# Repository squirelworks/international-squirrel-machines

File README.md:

# International Squirrel Machines (ISM)

Pure Squirrel-OS/2 Warp-style hardware development.

**International Squirrel Machines** is the hardware companion line to Squirrel-OS/2. All devices are designed and developed independently (contemporary sources studied only as reference). Designs live here as KiCad projects and parametric 3D-printable shells.

## Device Line

| Device | Status | Directory |
|--------|--------|-----------|
| Keyboard | Scaffolded | `keyboard/` |
| Mouse | Planned | `mouse/` |
| Monitor | Planned | `monitor/` |
| Computer Case | Planned | `case/` |
| Motherboard | Planned | `motherboard/` |
| CPU | Planned | `cpu/` |
| Memory (RAM modules) | Scaffolded | `memory/` |
| Graphics Card | Planned | `graphics-card/` |
| Typewriter | Planned | `typewriter/` |
| Printer | Planned | `printer/` |
| Plotter | Planned | `plotter/` |
| Camera | Planned | `camera/` |
| Trackball | Planned | `trackball/` |
| Sound Card | Planned | `sound-card/` |
| Network Card | Planned | `network-card/` |
| Terminal | Planned | `terminal/` |
| Macro Pad | Planned | `macro-pad/` |
| Drawing Pads (range) | Scaffolded | `drawing-pads/` |
| Fighter Jet | Design program | `fighter-jet/` |

## Repository Layout

```
international-squirrel-machines/
├── README.md
├── docs/
│   ├── roadmap.md
│   ├── design-principles.md
│   ├── branding.md
│   └── devices/
├── common/
│   ├── footprints/
│   ├── libraries/
│   └── branding/
├── keyboard/
│   ├── README.md
│   ├── kicad/
│   └── shell/
├── fighter-jet/
│   ├── README.md
│   ├── kicad/
│   └── shell/
└── [device]/
```

## Getting Started

1. Clone this repository.
2. Open device directories for KiCad projects or OpenSCAD shells.
3. See `docs/roadmap.md` for the current development sequence.
4. Issues track every device scaffold and implementation milestone.

## Philosophy

- Pure Squirrel-OS/2 development.
- When in doubt, scaffold.
- If scaffolded, implement.
- If implemented, polish.
- If polished, inquire for the next release.

Part of the Squirrelworks family alongside [squirrelbios](https://github.com/squirelworks/squirrelbios).

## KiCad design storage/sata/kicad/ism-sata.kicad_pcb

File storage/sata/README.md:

# ISM SATA

SATA carrier for commodity drives. Original International Squirrel Machines design.

Generate: `python3 scripts/build_sata.py` — **ERC 0 / DRC 0**.

## Layout

| Block | Notes |
|-------|--------|
| Host | USB-C (`J1`) bring-up |
| MCU | RP2040 module (`U1`) — DET / ACT |
| SATA | `ISM_SATA7` (`J2`) — GNDs wired; A/B pairs stubbed |
| Power | `J3` 1×4 drive +5V/GND (+12V external) |
| Shell | Carrier + lid |

## Fab ordering

1. `python3 scripts/build_sata.py`
2. Upload `storage/sata/fab/ism-sata-gerbers.zip`
3. SMT: CPL + `BOM.csv`
4. `cd storage/sata/shell && ./export.sh`

### Off-board BOM

- Commodity 2.5"/3.5" SATA drive
- M2 screws (4×)
- Optional external +12V for 3.5" spindles

## Flash

```bash
cd storage/sata/firmware
mkdir -p build && cd build && cmake .. && make -j
# copy ism_sata.uf2 to RPI-RP2
```

VID/PID **0x1209 / 0x001E**.

## Steve interface

See `interfaces/sata.yaml`.

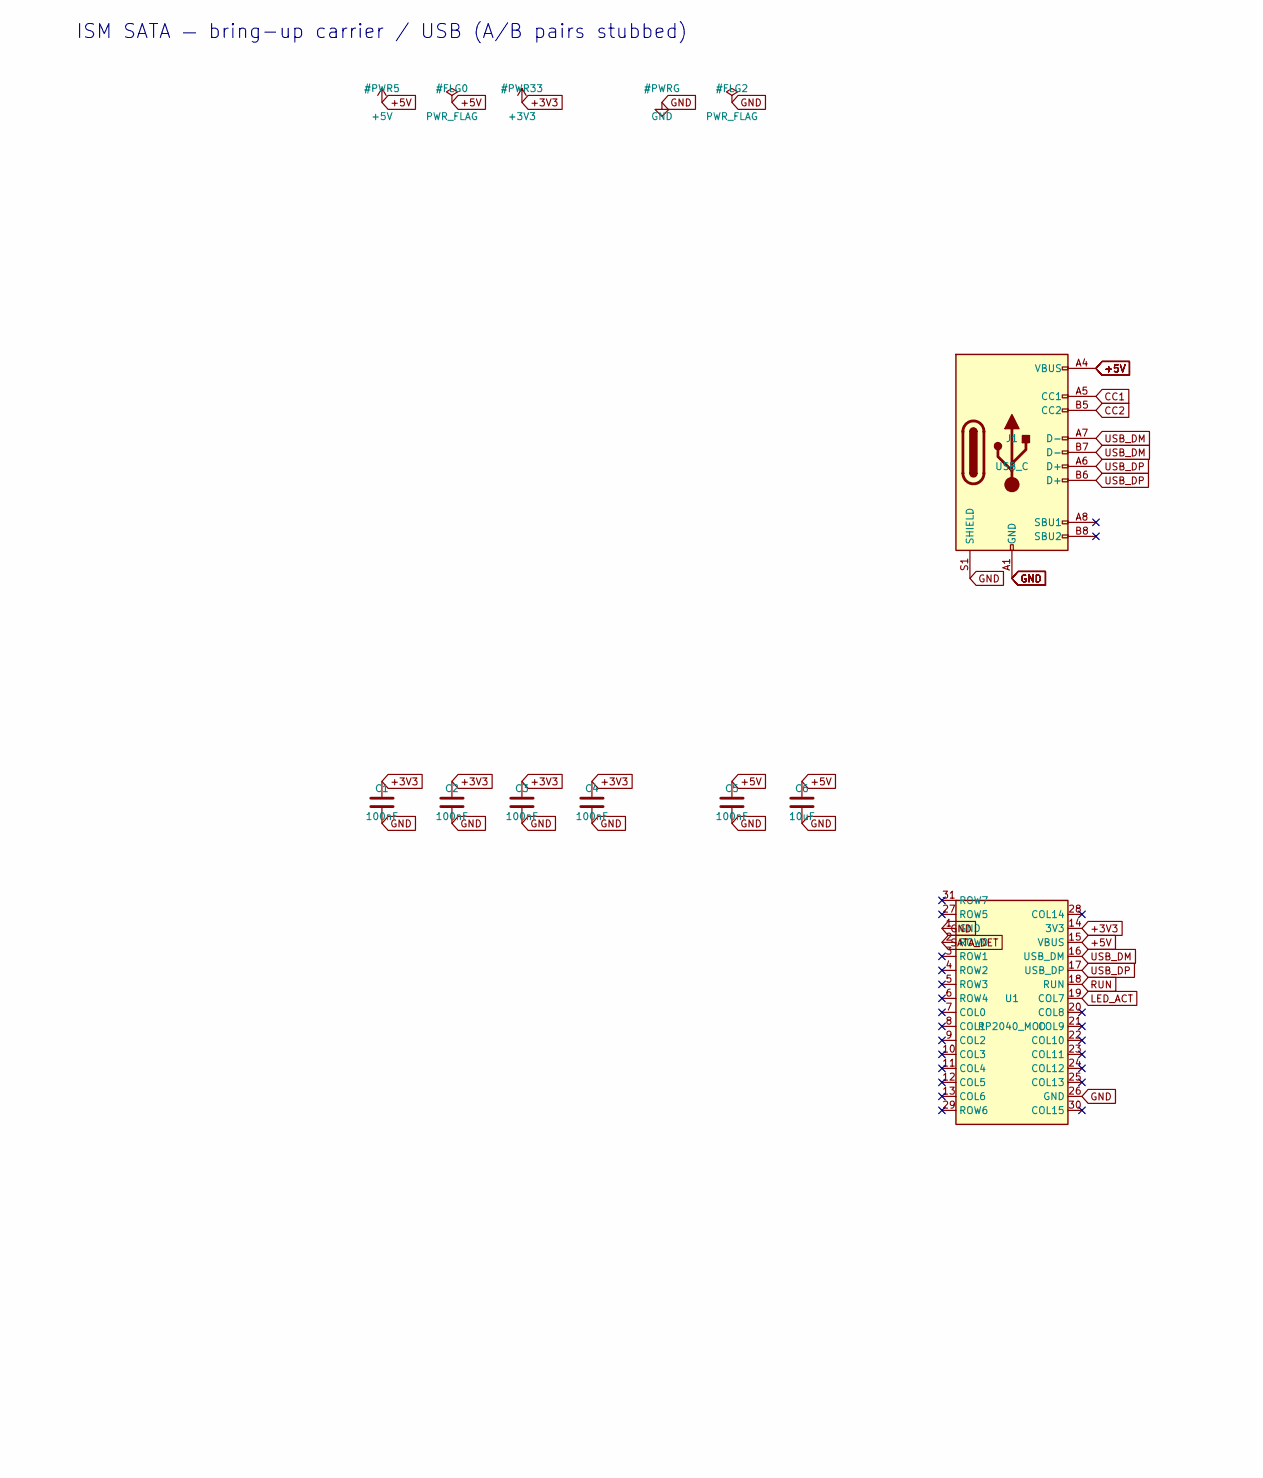
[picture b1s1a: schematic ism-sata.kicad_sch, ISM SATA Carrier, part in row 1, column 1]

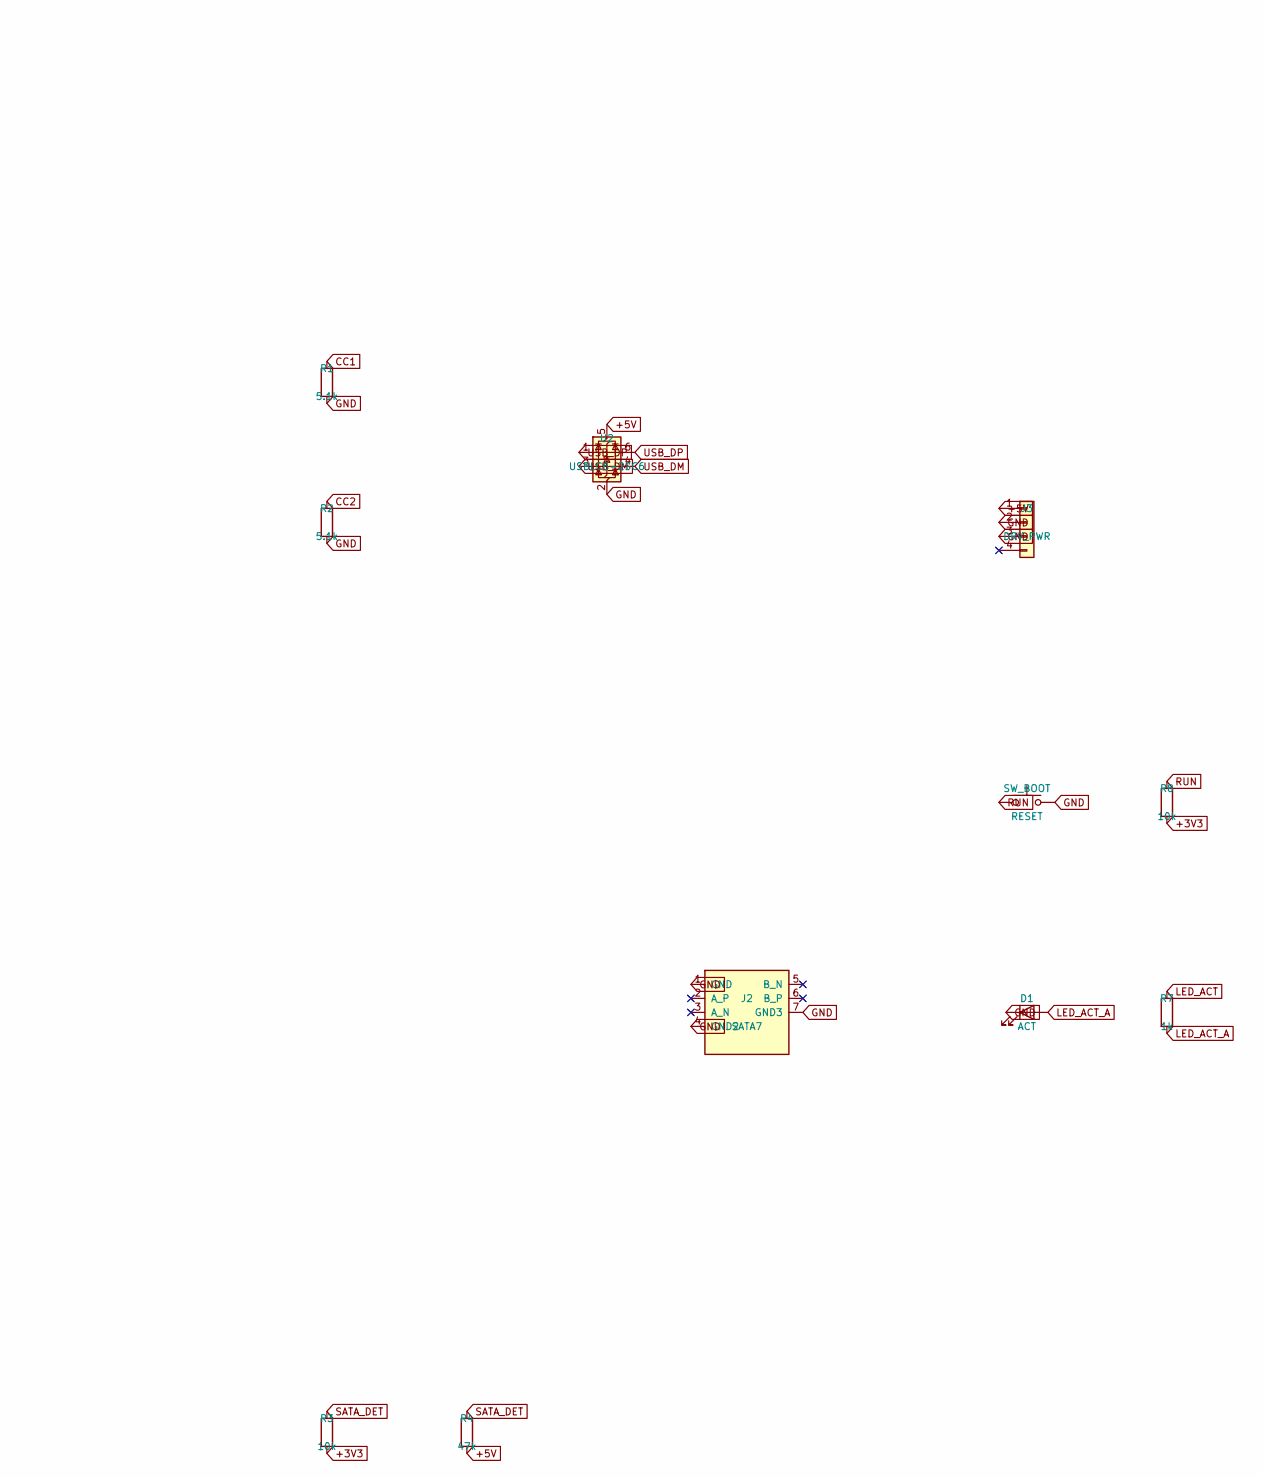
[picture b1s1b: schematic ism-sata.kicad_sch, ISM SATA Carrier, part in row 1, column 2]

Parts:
C1, C2, C3, C4, C5: 100nF; C_0603_1608Metric; LCSC C14663
C6: 10uF; C_0805_2012Metric; LCSC C15850
D1: ACT; LED_0603_1608Metric; LCSC C2286
J1: USB_C; USB_C_Receptacle_GCT_USB4105-xx-A_16P_TopMnt_Horizontal; LCSC C165948
J2: SATA7; ISM_SATA7; MPN ISM-SATA7
J3: DRV_PWR; PinHeader_1x04_P2.54mm_Vertical
R1, R2: 5.1k; R_0603_1608Metric; LCSC C23244
R3, R8: 10k; R_0603_1608Metric; LCSC C25804
R4: 47k; R_0603_1608Metric; LCSC C25803
R7: 1k; R_0603_1608Metric; LCSC C21190
SW_BOOT: RESET; SW_SPST_PTS645; LCSC C318884
U1: RP2040_MOD; ISM_RP2040_Module; MPN ISM-RP2040-MOD
U2: USBLC6-2SC6; SOT-666; LCSC C7519

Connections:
+3V3: C1.1, C2.1, C3.1, C4.1, R3.2, R8.2, U1.14 (3V3)
+5V: C5.1, C6.1, J1.A4 (VBUS), J1.A9 (VBUS), J1.B4 (VBUS), J1.B9 (VBUS), J3.1, R4.2, U1.15 (VBUS), U2.5 (VBUS)
CC1: J1.A5 (CC1), R1.1
CC2: J1.B5 (CC2), R2.1
GND: C1.2, C2.2, C3.2, C4.2, C5.2, C6.2, D1.1 (K), J1.A1 (GND), J1.A12 (GND), J1.B1 (GND), J1.B12 (GND), J1.S1 (SHIELD), J2.1 (GND), J2.4 (GND2), J2.7 (GND3), J3.2, J3.3, R1.2, R2.2, SW_BOOT.2, U1.1 (GND), U1.26 (GND), U2.2 (GND)
LED_ACT: R7.1, U1.19 (COL7)
LED_ACT_A: D1.2 (A), R7.2
RUN: R8.1, SW_BOOT.1, U1.18 (RUN)
SATA_DET: R3.1, R4.1, U1.2 (ROW0)
USB_DM: J1.A7 (D-), J1.B7 (D-), U1.16 (USB_DM), U2.3 (I/O2), U2.4 (I/O2)
USB_DP: J1.A6 (D+), J1.B6 (D+), U1.17 (USB_DP), U2.1 (I/O1), U2.6 (I/O1)

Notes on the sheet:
ISM SATA — bring-up carrier / USB (A/B pairs stubbed)

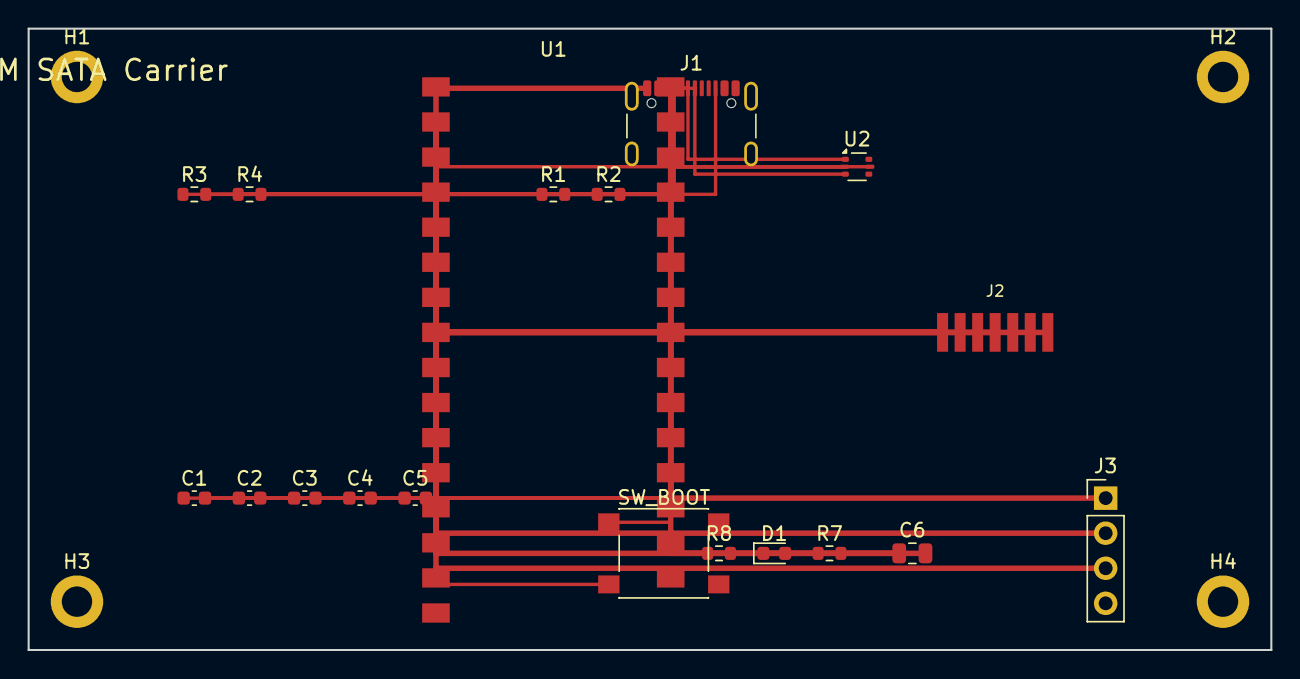
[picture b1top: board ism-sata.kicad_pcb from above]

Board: 4 copper layers, 90.0 x 45.0 mm, 23 parts (0 on the bottom side), 11 nets.

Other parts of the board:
H1, H2, H3, H4: M2; MountingHole_2.2mm_M2_DIN965_Pad

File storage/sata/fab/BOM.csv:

Designator,Value,Footprint,Quantity,Manufacturer,MPN,LCSC,Notes
U1,RP2040_MOD,ISM_RP2040_Module,1,ISM,ISM-RP2040-MOD,,No LCSC — activity / DET controller
U2,USBLC6-2SC6,SOT-666,1,ST,USBLC6-2SC6,C7519,ESD
J1,USB4105,GCT USB-C 16P,1,GCT,USB4105-GF-A,C165948,
J2,ISM_SATA7,ISM_SATA7,1,ISM,ISM-SATA7,,No LCSC — simplified SATA data; fab as custom or substitute SATA receptacle
J3,1x04,PinHeader_1x04,1,,,,Drive +5V/GND (+12V external)
"R1,R2",5.1k,0603,2,,5.1k,C23244,CC
"R3,R8",10k,0603,2,,10k,C25804,
R4,47k,0603,1,,47k,C25803,DET from +5V
R7,1k,0603,1,,1k,C21190,
C1-C5,100nF,0603,5,,100nF,C14663,
C6,10uF,0805,1,,10uF,C15850,
D1,LED,0603,1,,LED,C2286,
SW_BOOT,PTS645,PTS645,1,,PTS645,C318884,
H1-H4,M2,MountingHole,4,,,,No LCSC — mechanical NPTH

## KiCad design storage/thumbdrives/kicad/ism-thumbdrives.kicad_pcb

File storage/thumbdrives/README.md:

# ISM Thumb Drives

USB-MSC stick board wrapping commodity SPI NOR flash. Original International Squirrel Machines design.

Generate: `python3 scripts/build_thumbdrives.py` — **ERC 0 / DRC 0**.

## Layout

| Block | Notes |
|-------|--------|
| Host | USB-C (`J1`) bring-up |
| MCU | RP2040 module (`U1`) — SPI master / MSC controller |
| Media | Winbond **W25Q32JVSS** SOIC-8 (`U3`, LCSC **C82307**) |
| Shell | Stick body + end cap |

## Fab ordering

1. `python3 scripts/build_thumbdrives.py`
2. Upload `storage/thumbdrives/fab/ism-thumbdrives-gerbers.zip`
3. SMT: CPL + `BOM.csv`
4. `cd storage/thumbdrives/shell && ./export.sh`

### Off-board BOM

- M2 screws (4×)

## Flash

```bash
cd storage/thumbdrives/firmware
mkdir -p build && cd build && cmake .. && make -j
# copy ism_thumbdrives.uf2 to RPI-RP2
```

VID/PID **0x1209 / 0x001A**.

## Steve interface

See `interfaces/thumbdrives.yaml`. Activity LED heartbeat until MSC lands.

## Related

- [#53](https://github.com/squirelworks/international-squirrel-machines/issues/53) · umbrella [#49](https://github.com/squirelworks/international-squirrel-machines/issues/49)
- Follow-ups: [#225](https://github.com/squirelworks/international-squirrel-machines/issues/225)

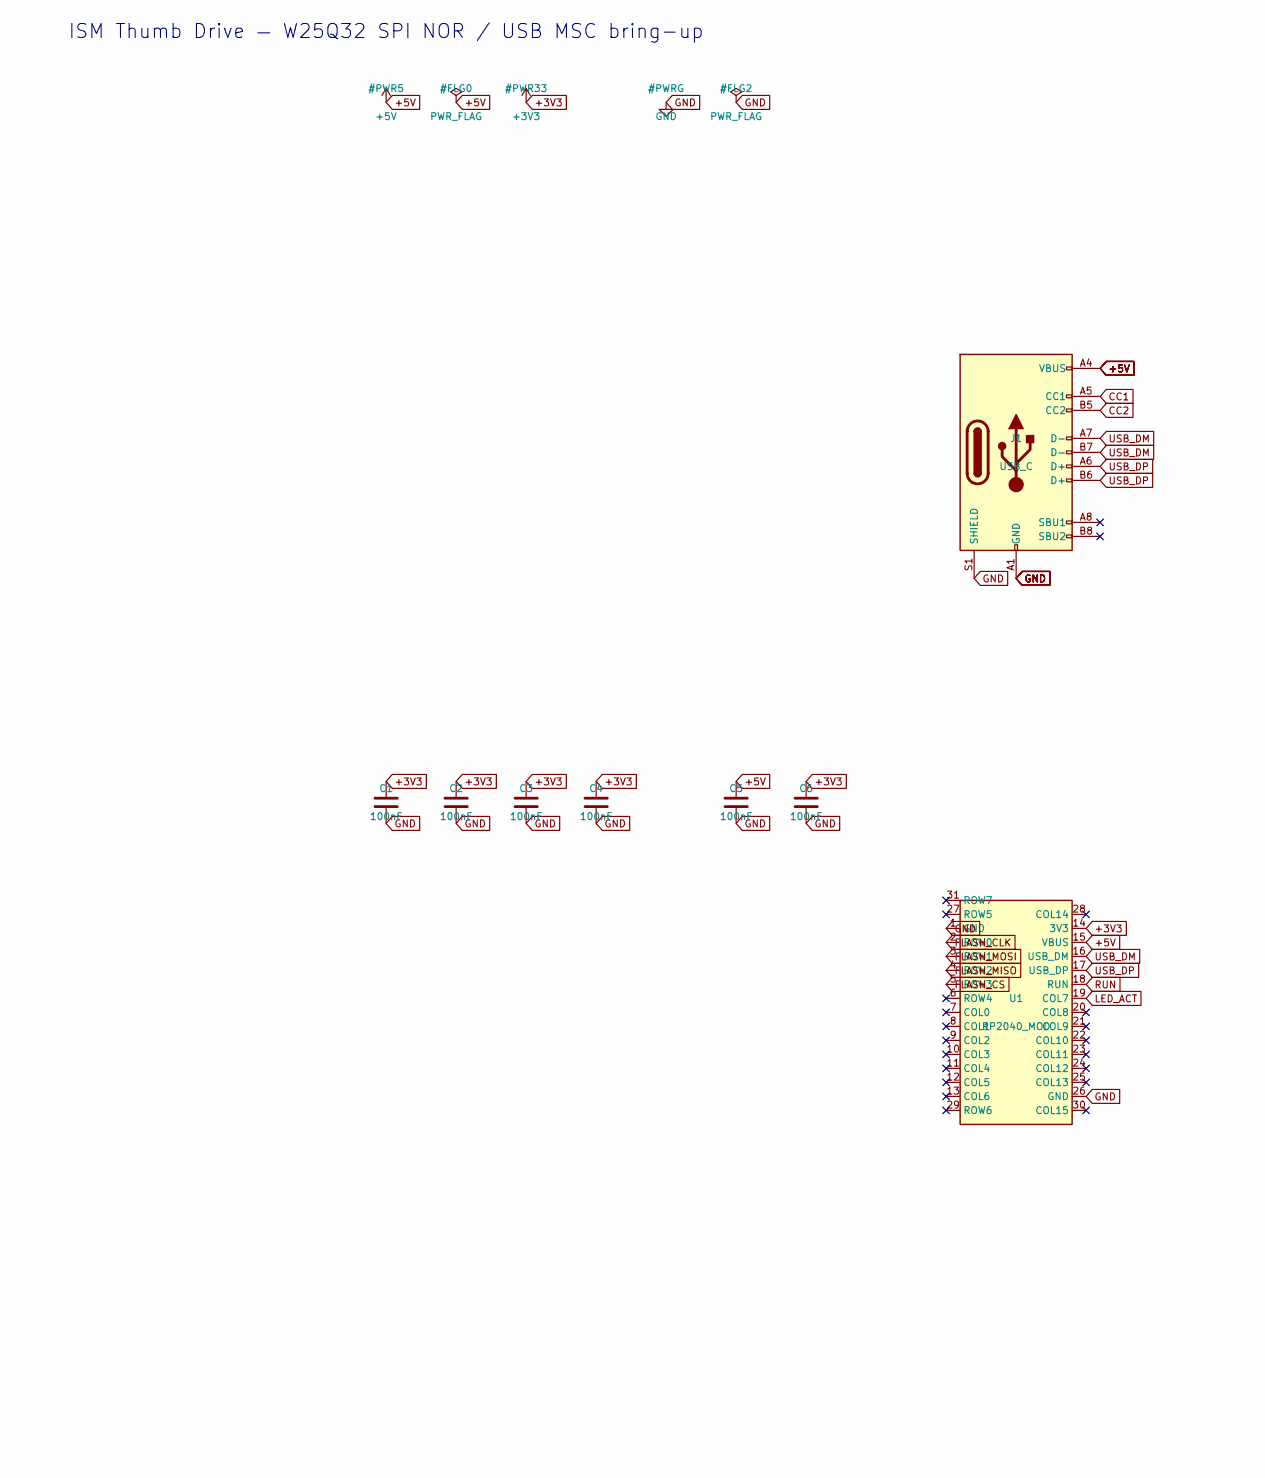
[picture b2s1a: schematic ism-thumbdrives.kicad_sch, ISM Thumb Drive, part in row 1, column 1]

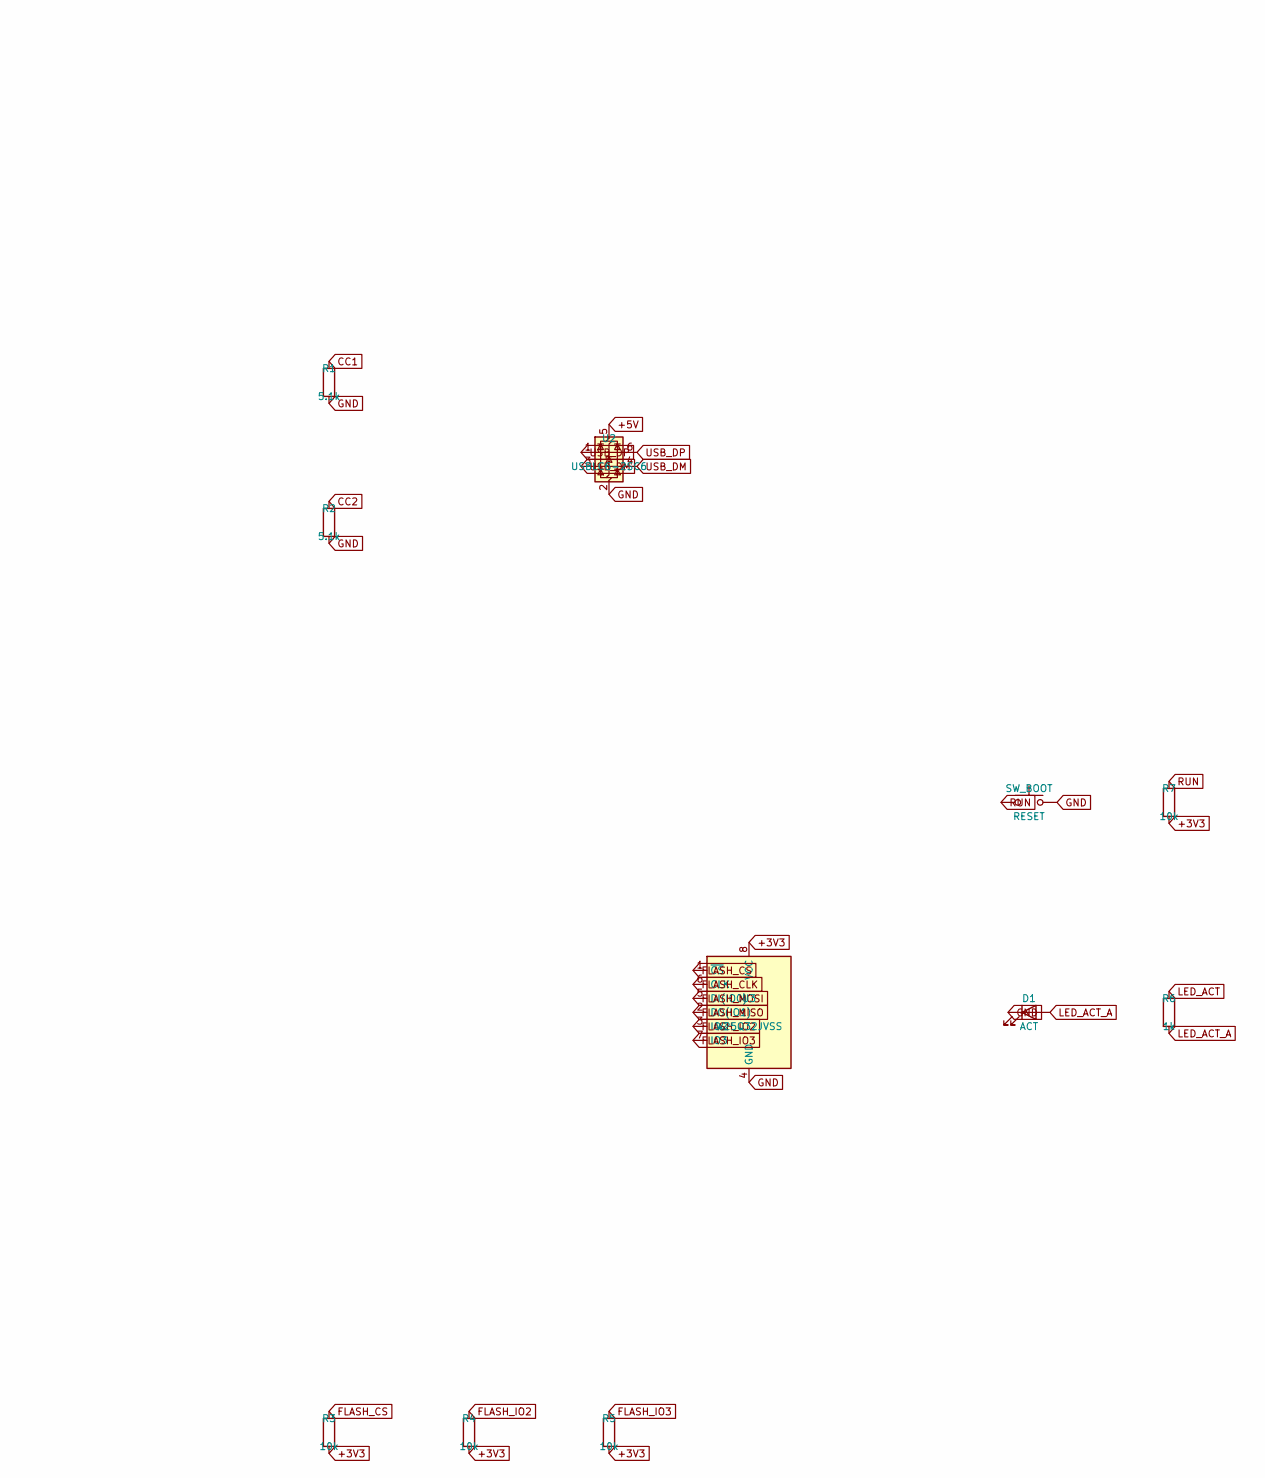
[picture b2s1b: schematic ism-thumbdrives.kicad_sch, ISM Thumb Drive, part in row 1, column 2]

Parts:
C1, C2, C3, C4, C5, C6: 100nF; C_0603_1608Metric; LCSC C14663
D1: ACT; LED_0603_1608Metric; LCSC C2286
J1: USB_C; USB_C_Receptacle_GCT_USB4105-xx-A_16P_TopMnt_Horizontal; LCSC C165948
R1, R2: 5.1k; R_0603_1608Metric; LCSC C23244
R3, R4, R5, R7: 10k; R_0603_1608Metric; LCSC C25804
R6: 1k; R_0603_1608Metric; LCSC C21190
SW_BOOT: RESET; SW_SPST_PTS645; LCSC C318884
U1: RP2040_MOD; ISM_RP2040_Module; MPN ISM-RP2040-MOD
U2: USBLC6-2SC6; SOT-666; LCSC C7519
U3: W25Q32JVSS; SOIC-8_3.9x4.9mm_P1.27mm; MPN W25Q32JVSSIQ; LCSC C82307

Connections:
+3V3: C1.1, C2.1, C3.1, C4.1, C6.1, R3.2, R4.2, R5.2, R7.2, U1.14 (3V3), U3.8 (VCC)
+5V: C5.1, J1.A4 (VBUS), J1.A9 (VBUS), J1.B4 (VBUS), J1.B9 (VBUS), U1.15 (VBUS), U2.5 (VBUS)
CC1: J1.A5 (CC1), R1.1
CC2: J1.B5 (CC2), R2.1
FLASH_CLK: U1.2 (ROW0), U3.6 (CLK)
FLASH_CS: R3.1, U1.5 (ROW3), U3.1 (~CS)
FLASH_IO2: R4.1, U3.3 (IO2)
FLASH_IO3: R5.1, U3.7 (IO3)
FLASH_MISO: U1.4 (ROW2), U3.2 (DO(IO1))
FLASH_MOSI: U1.3 (ROW1), U3.5 (DI(IO0))
GND: C1.2, C2.2, C3.2, C4.2, C5.2, C6.2, D1.1 (K), J1.A1 (GND), J1.A12 (GND), J1.B1 (GND), J1.B12 (GND), J1.S1 (SHIELD), R1.2, R2.2, SW_BOOT.2, U1.1 (GND), U1.26 (GND), U2.2 (GND), U3.4 (GND)
LED_ACT: R6.1, U1.19 (COL7)
LED_ACT_A: D1.2 (A), R6.2
RUN: R7.1, SW_BOOT.1, U1.18 (RUN)
USB_DM: J1.A7 (D-), J1.B7 (D-), U1.16 (USB_DM), U2.3 (I/O2), U2.4 (I/O2)
USB_DP: J1.A6 (D+), J1.B6 (D+), U1.17 (USB_DP), U2.1 (I/O1), U2.6 (I/O1)

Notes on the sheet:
ISM Thumb Drive — W25Q32 SPI NOR / USB MSC bring-up

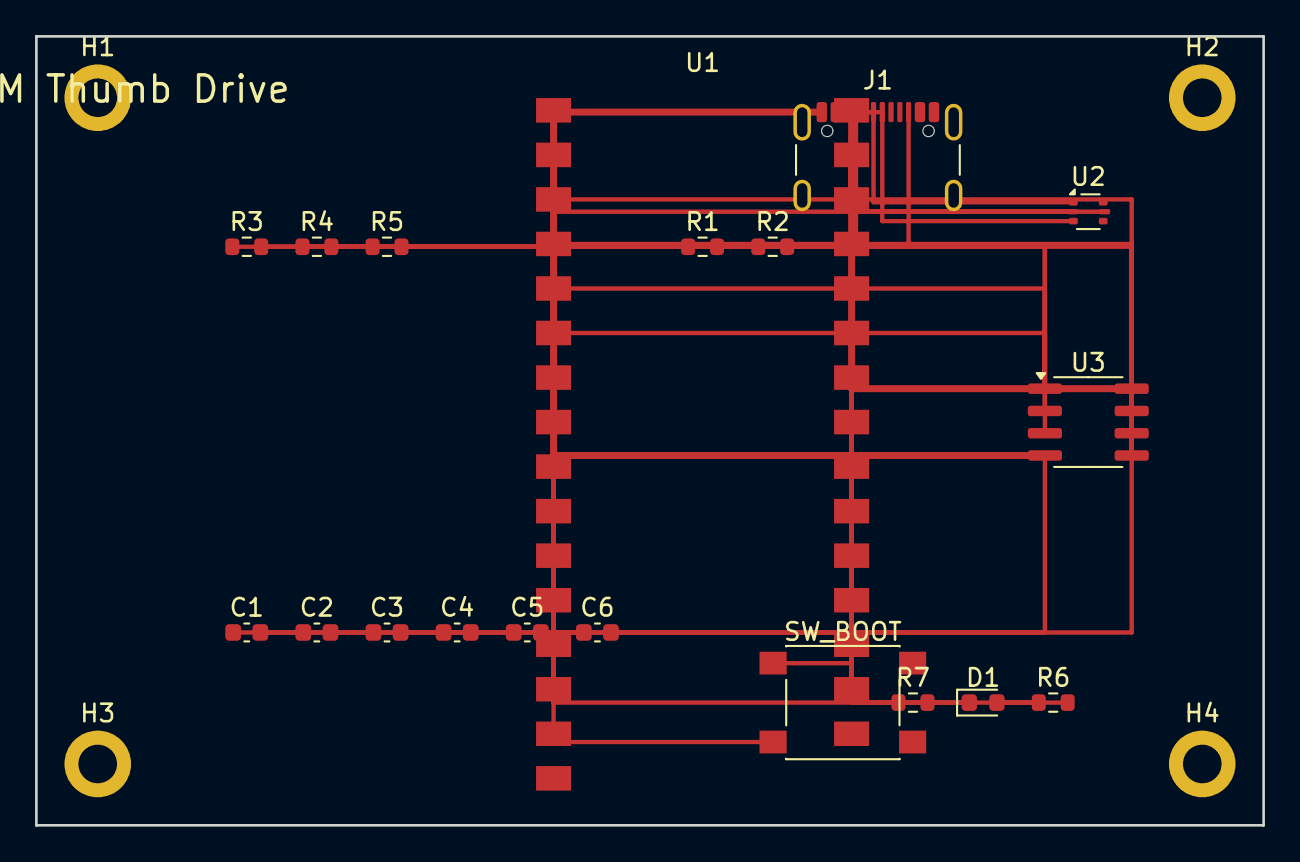
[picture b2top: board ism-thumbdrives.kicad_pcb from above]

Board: 4 copper layers, 70.0 x 45.0 mm, 23 parts (0 on the bottom side), 16 nets.

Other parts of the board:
H1, H2, H3, H4: M2; MountingHole_2.2mm_M2_DIN965_Pad

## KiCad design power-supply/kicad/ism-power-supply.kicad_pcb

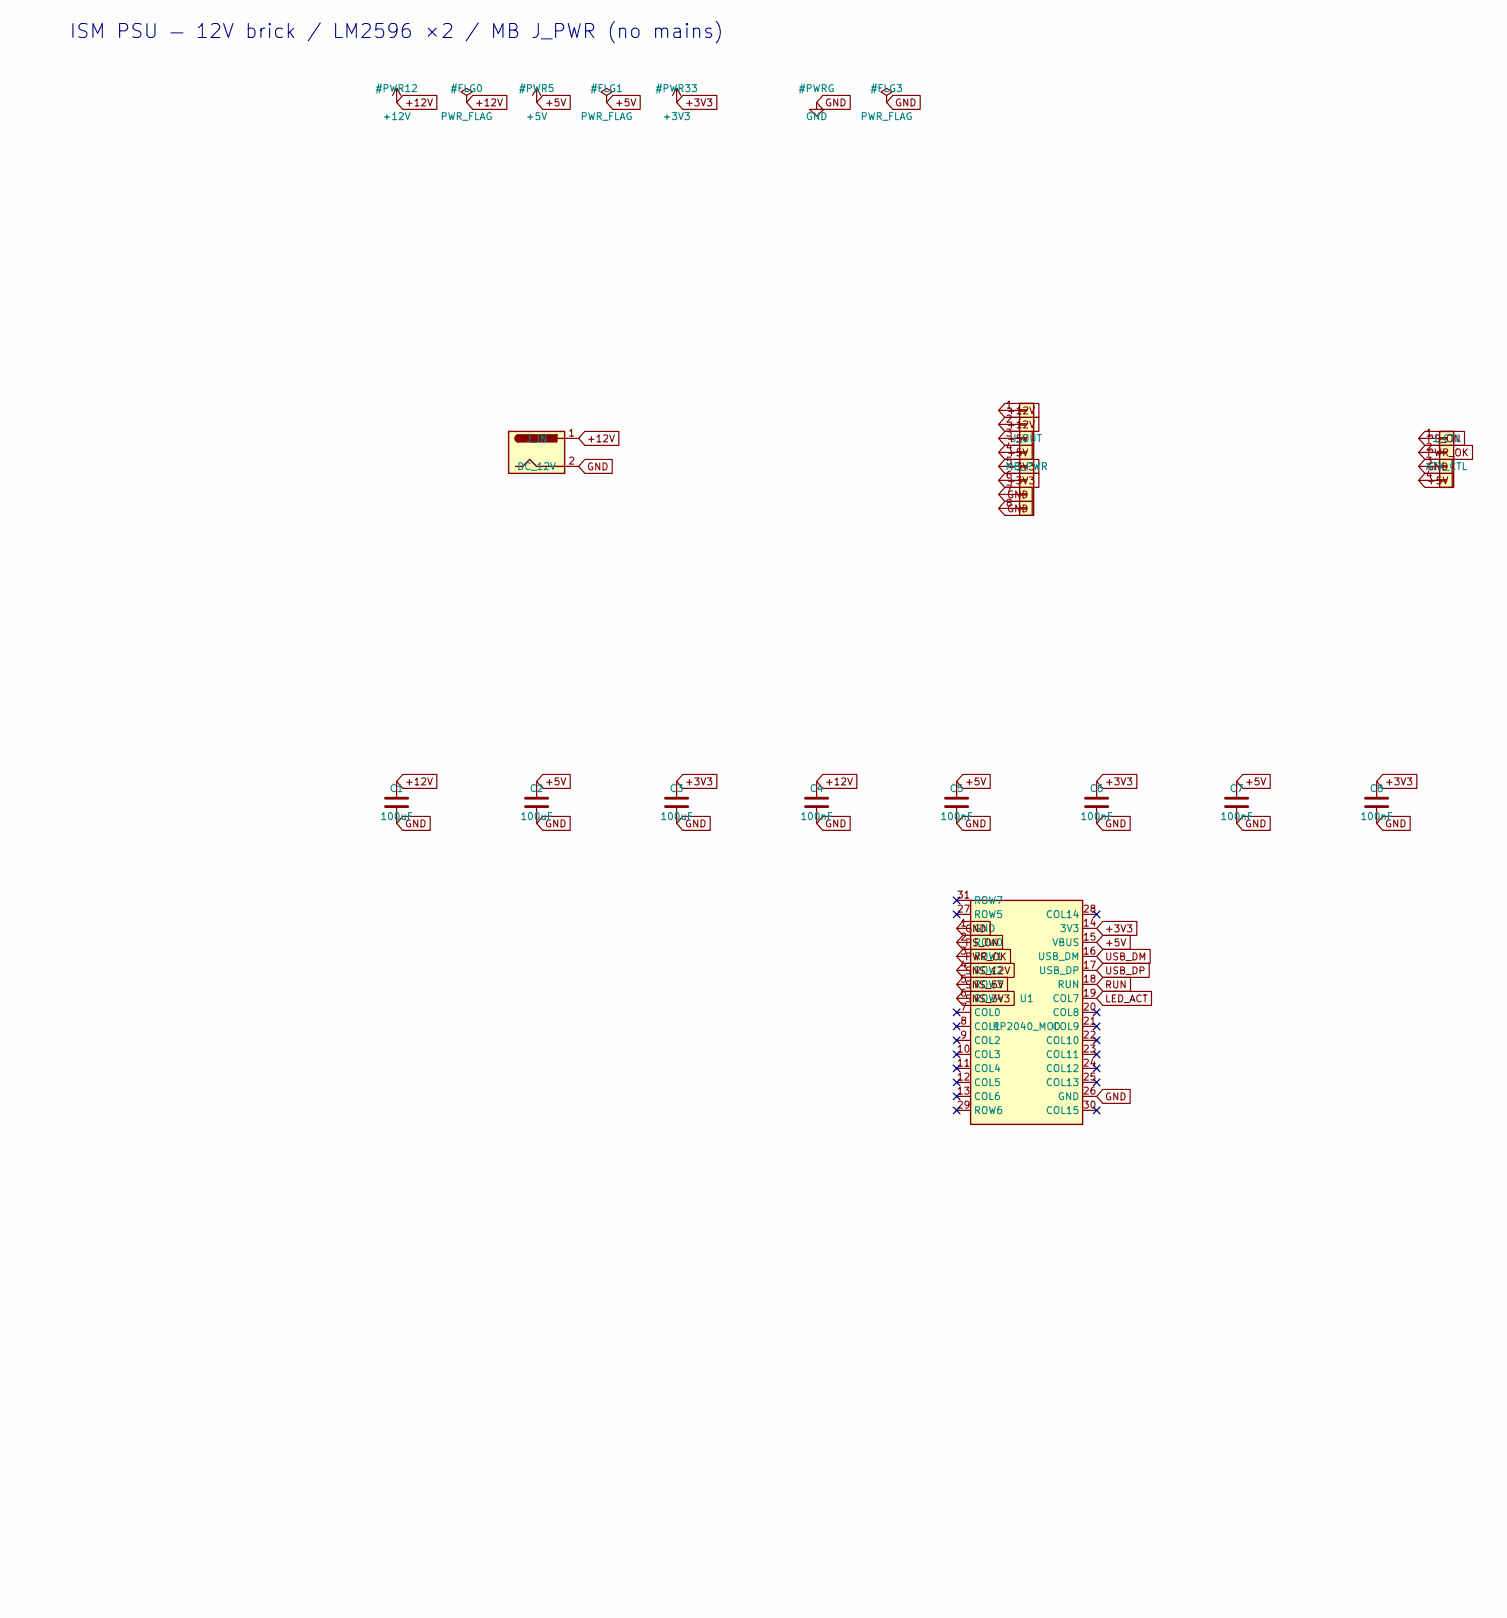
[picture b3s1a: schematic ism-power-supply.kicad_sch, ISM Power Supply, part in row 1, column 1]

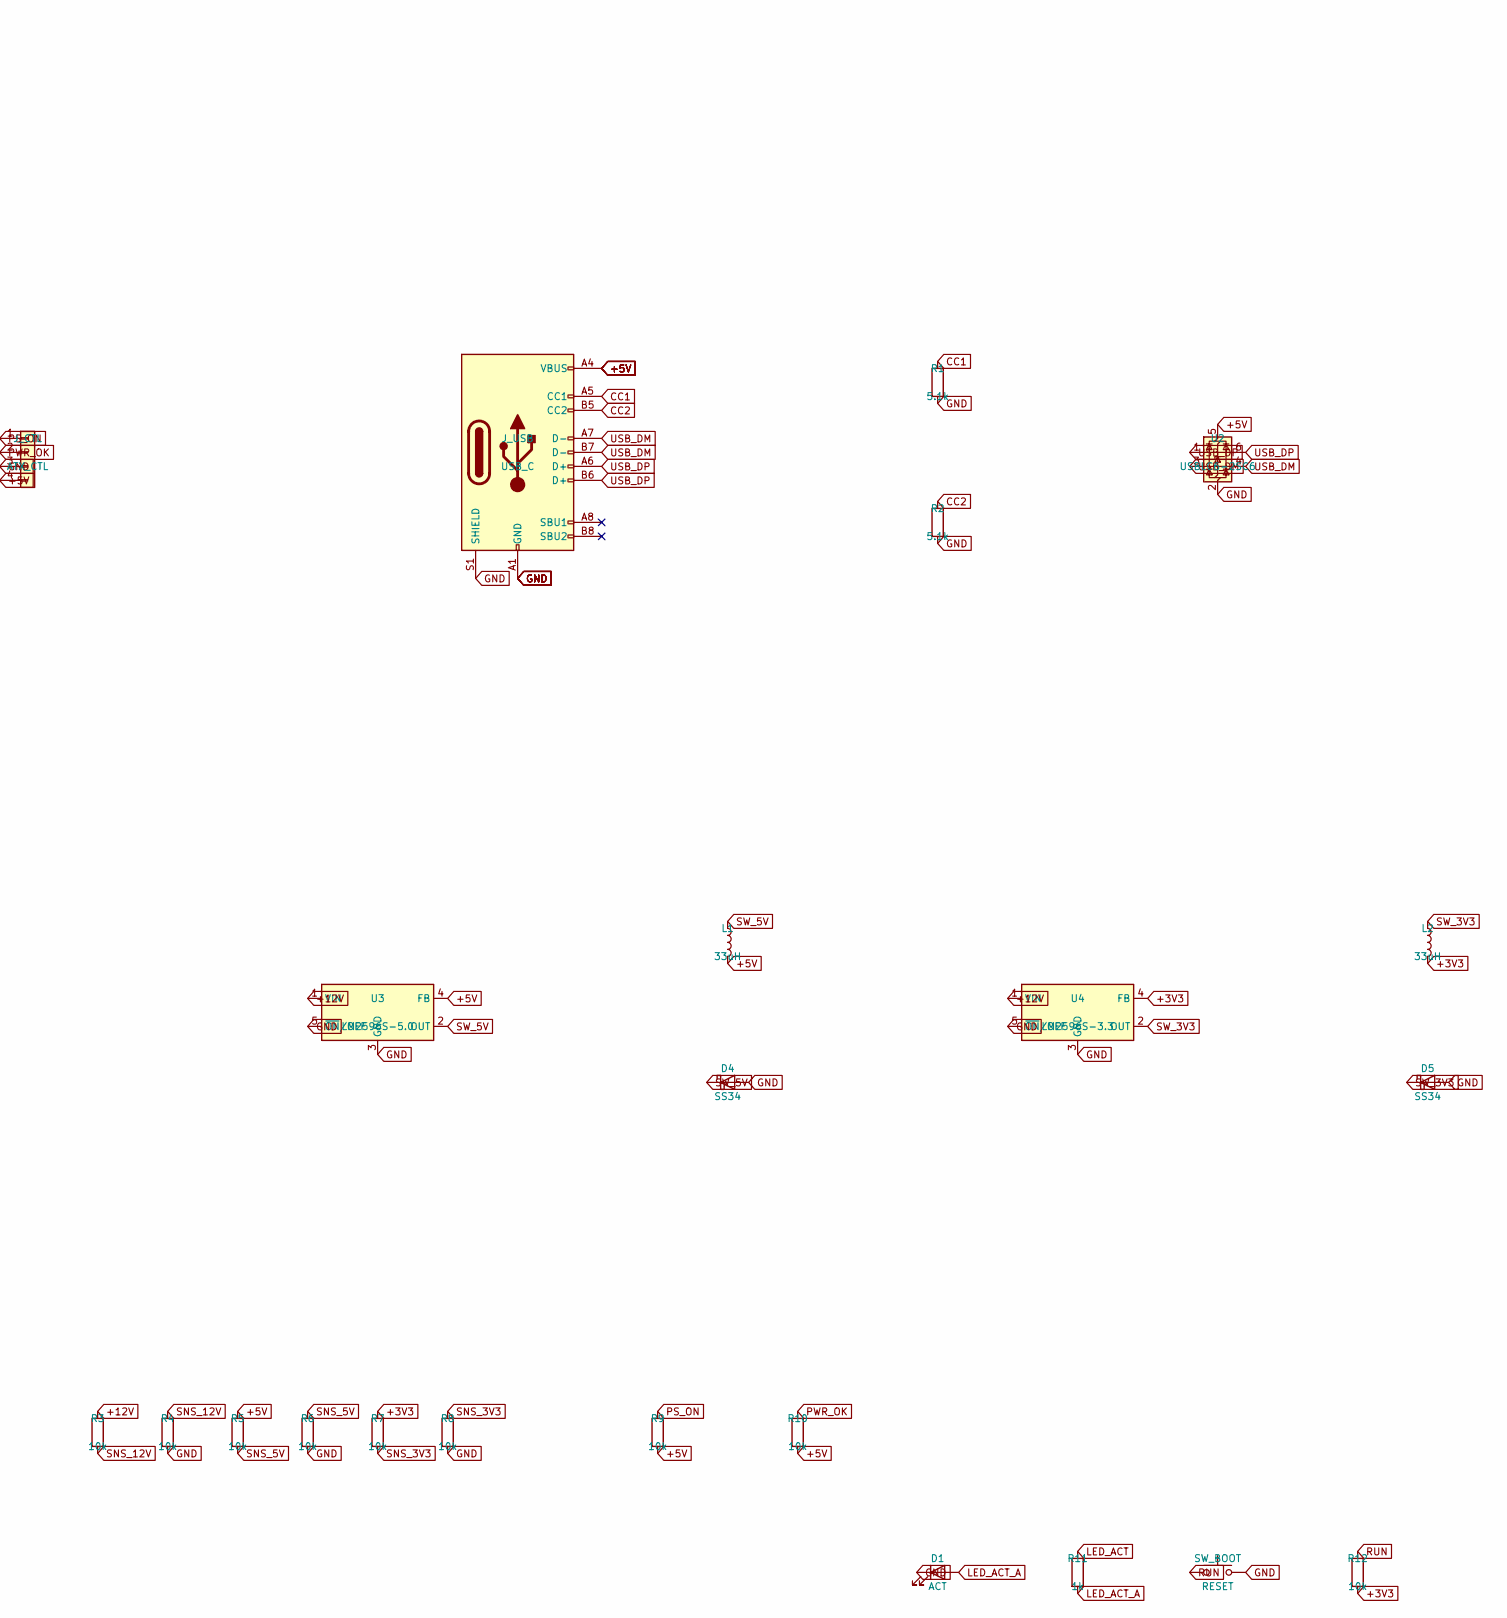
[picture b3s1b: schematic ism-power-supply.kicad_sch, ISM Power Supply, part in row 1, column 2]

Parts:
C1, C2, C3: 100uF; C_0603_1608Metric; LCSC C15855
C4, C5, C6, C7, C8: 100nF; C_0603_1608Metric; LCSC C14663
D1: ACT; LED_0603_1608Metric; LCSC C2286
D4, D5: SS34; D_SMA; LCSC C8678
J_CTL: ATX_CTL; PinHeader_1x04_P2.54mm_Vertical; LCSC C124409
J_IN: DC_12V; BarrelJack_CUI_PJ-063AH_Horizontal; LCSC C75013
J_OUT: MB_PWR; PinHeader_1x08_P2.54mm_Vertical; LCSC C124412
J_USB: USB_C; USB_C_Receptacle_GCT_USB4105-xx-A_16P_TopMnt_Horizontal; LCSC C165948
L1, L2: 33uH; L_12x12mm_H6mm; LCSC C167270
R1, R2: 5.1k; R_0603_1608Metric; LCSC C23244
R3, R4, R5, R6, R7, R8, R9, R10, R12: 10k; R_0603_1608Metric; LCSC C25804
R11: 1k; R_0603_1608Metric; LCSC C21190
SW_BOOT: RESET; SW_SPST_PTS645; LCSC C318884
U1: RP2040_MOD; ISM_RP2040_Module; MPN ISM-RP2040-MOD
U2: USBLC6-2SC6; SOT-666; LCSC C7519
U3: LM2596S-5.0; TO-263-5_TabPin3; MPN LM2596S-5.0; LCSC C10872
U4: LM2596S-3.3; TO-263-5_TabPin3; MPN LM2596S-3.3; LCSC C10871

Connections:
+3V3: C3.1, C6.1, C8.1, J_OUT.5, J_OUT.6, L2.2, R7.1, R12.2, U1.14 (3V3), U4.4 (FB)
+5V: C2.1, C5.1, C7.1, J_CTL.4, J_OUT.3, J_OUT.4, J_USB.A4 (VBUS), J_USB.A9 (VBUS), J_USB.B4 (VBUS), J_USB.B9 (VBUS), L1.2, R5.1, R9.2, R10.2, U1.15 (VBUS), U2.5 (VBUS), U3.4 (FB)
+12V: C1.1, C4.1, J_IN.1, J_OUT.1, J_OUT.2, R3.1, U3.1 (VIN), U4.1 (VIN)
CC1: J_USB.A5 (CC1), R1.1
CC2: J_USB.B5 (CC2), R2.1
GND: C1.2, C2.2, C3.2, C4.2, C5.2, C6.2, C7.2, C8.2, D1.1 (K), D4.2 (A), D5.2 (A), J_CTL.3, J_IN.2, J_OUT.7, J_OUT.8, J_USB.A1 (GND), J_USB.A12 (GND), J_USB.B1 (GND), J_USB.B12 (GND), J_USB.S1 (SHIELD), R1.2, R2.2, R4.2, R6.2, R8.2, SW_BOOT.2, U1.1 (GND), U1.26 (GND), U2.2 (GND), U3.3 (GND), U3.5 (~ON/OFF), U4.3 (GND), U4.5 (~ON/OFF)
LED_ACT: R11.1, U1.19 (COL7)
LED_ACT_A: D1.2 (A), R11.2
PS_ON: J_CTL.1, R9.1, U1.2 (ROW0)
PWR_OK: J_CTL.2, R10.1, U1.3 (ROW1)
RUN: R12.1, SW_BOOT.1, U1.18 (RUN)
SNS_3V3: R7.2, R8.1, U1.6 (ROW4)
SNS_5V: R5.2, R6.1, U1.5 (ROW3)
SNS_12V: R3.2, R4.1, U1.4 (ROW2)
SW_3V3: D5.1 (K), L2.1, U4.2 (OUT)
SW_5V: D4.1 (K), L1.1, U3.2 (OUT)
USB_DM: J_USB.A7 (D-), J_USB.B7 (D-), U1.16 (USB_DM), U2.3 (I/O2), U2.4 (I/O2)
USB_DP: J_USB.A6 (D+), J_USB.B6 (D+), U1.17 (USB_DP), U2.1 (I/O1), U2.6 (I/O1)

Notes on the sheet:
ISM PSU — 12V brick / LM2596 ×2 / MB J_PWR (no mains)

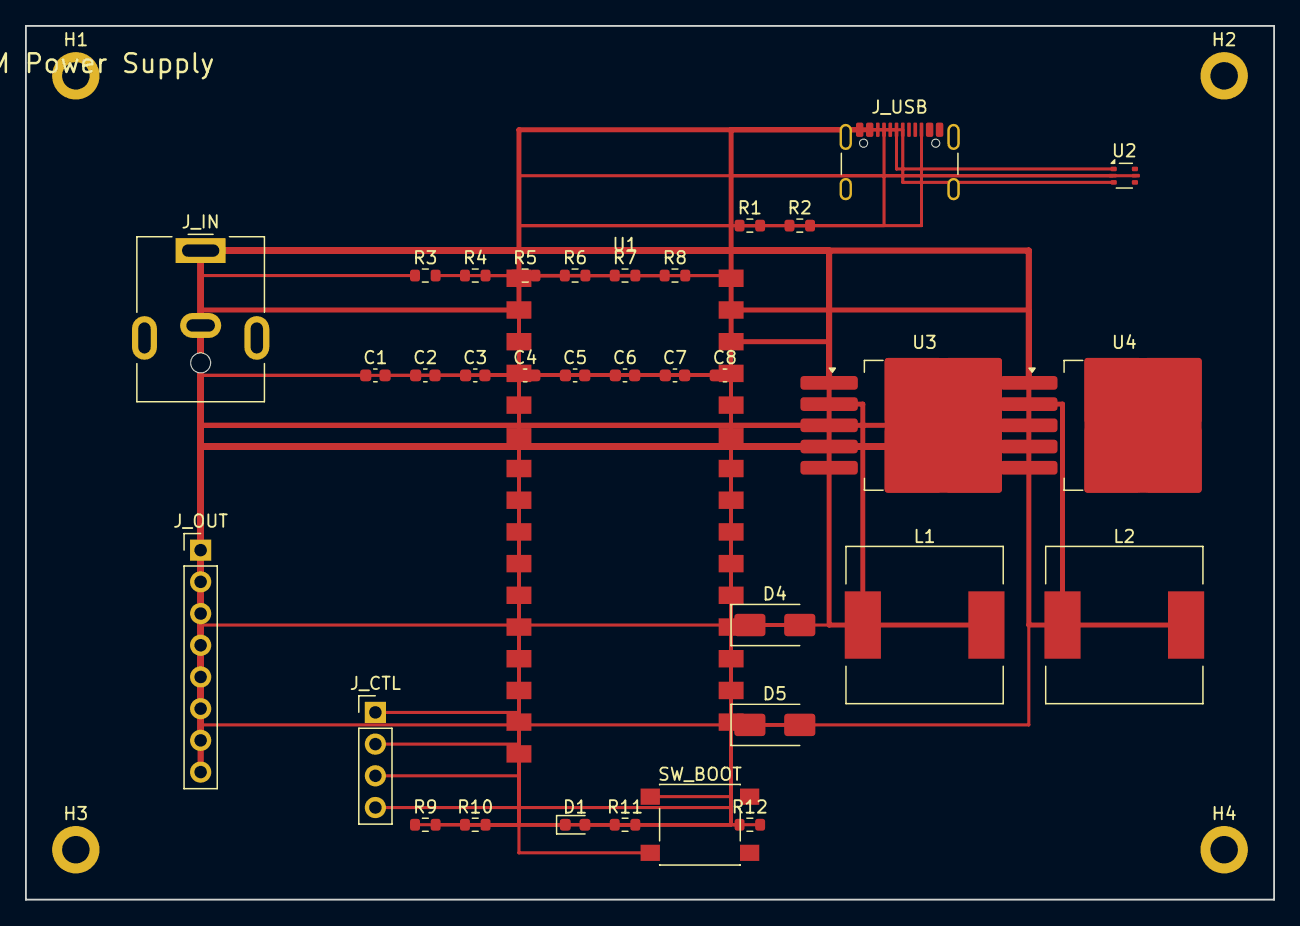
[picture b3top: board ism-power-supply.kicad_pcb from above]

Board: 4 copper layers, 100.0 x 70.0 mm, 38 parts (0 on the bottom side), 18 nets.

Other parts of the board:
H1, H2, H3, H4: M2; MountingHole_2.2mm_M2_DIN965_Pad

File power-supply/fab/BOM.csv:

Designator,Value,Footprint,Quantity,Manufacturer,MPN,LCSC,Notes
U1,RP2040_MOD,ISM_RP2040_Module,1,ISM,ISM-RP2040-MOD,,No LCSC — PSU monitor
U2,USBLC6-2SC6,SOT-666,1,ST,USBLC6-2SC6,C7519,ESD
U3,LM2596S-5.0,TO-263-5,1,TI,LM2596S-5.0,C10872,+5V buck
U4,LM2596S-3.3,TO-263-5,1,TI,LM2596S-3.3,C10871,+3V3 buck
J_IN,PJ-063AH,CUI barrel,1,CUI,PJ-063AH,C75013,12V from brick
J_OUT,MB_PWR,PinHeader 1x08,1,,HDR-1x8,C124412,To motherboard J_PWR
J_CTL,ATX_CTL,PinHeader 1x04,1,,HDR-1x4,C124409,PS_ON/PWR_OK
J_USB,USB4105,GCT USB-C 16P,1,GCT,USB4105-GF-A,C165948,
"L1,L2",33uH,12x12mm,2,,33uH,C167270,Buck inductors
"D4,D5",SS34,SMA,2,,SS34,C8678,Catch diodes
"R1,R2",5.1k,0603,2,,5.1k,C23244,CC
"R3-R10,R12",10k,0603,9,,10k,C25804,Sense/pull
R11,1k,0603,1,,1k,C21190,
C1-C3,100uF,0603,3,,100uF,C15855,Bulk
C4-C8,100nF,0603,5,,100nF,C14663,
D1,LED,0603,1,,LED,C2286,
SW_BOOT,PTS645,PTS645,1,,PTS645,C318884,
H1-H4,M2,MountingHole,4,,,,No LCSC — mechanical NPTH
